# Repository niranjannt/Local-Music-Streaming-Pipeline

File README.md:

# Local Music Streaming Pipeline (ECE 445L Final Project)

This repository contains the final project for **Embedded Design Laboratory (ECE 445L)** at **UT Austin**, developed by Niranjan Telkikar, Ashton Knecht, Thompson Truong, and Nathan DeLaRosa. The project implements a music-streaming pipeline using local WAV files, combining frontend/backend software with embedded hardware.

## Project Overview

Our system streams music from a web interface to an **ESP32-Devkit-V1** and outputs audio through a **12-bit SPI DAC** connected to a headphone jack. The pipeline includes both **analog and digital filters** controlled in real-time by circular potentiometers, allowing adjustment of treble, mid, bass, and digital effects such as flanger, distortion, and reverb.

### Pipeline Flow

1. **Web Interface**: Streams WAV files via Java Serial library to the ESP32 through a USB-UART converter.  
2. **ESP32**: Receives serial data and sends it to the SPI DAC (mono channel). It also handles digital filter adjustments.  
3. **DAC**: Outputs analog audio to headphones.  
4. **TM4C123GH6PM**: Reads potentiometer inputs for analog filters and adjusts MOSFET gain circuits for treble, mid, and bass channels in real-time.  
5. **Visualizer**: Displays right-bass changes in real-time using ADC input from the TM4C.

---

## Team Contributions

- **Ashton Knecht**:  
  - Designed and soldered the PCB with ESP32-Devkit-V1.  
  - Implemented MOSFET gain circuits for analog filters.  
  - Carefully routed PCB to minimize trace length.

- **Thompson Truong**:  
  - Designed the enclosure and circular potentiometers for analog and digital filter control.  
  - Developed ESP-IDF code for digital filters on the ESP32 and analog filters on the TM4C.

- **Nathan DeLaRosa**:  
  - Implemented audio playback and backend/frontend for the web interface.  
  - Wrote ESP-IDF code for streaming audio.

- **Niranjan Telkikar**:  
  - Wrote and tested the **mono DAC_Out function** for the ESP32 (Arduino IDE/ESP-IDF).  
  - Developed a basic visualizer for real-time bass monitoring.  
  - Assisted with hardware debugging and ESP-IDF integration.

---

## Hardware Components

- ESP32-Devkit-V1  
- TM4C123GH6PM microcontroller  
- 12-bit SPI DAC (mono)  
- MOSFET-based analog gain circuits  
- Circular potentiometers for analog and digital filters  
- Headphone jack for output audio

---

## Software Components

- Arduino IDE / ESP-IDF framework for microcontroller programming  
- Java Serial library for web-to-ESP32 streaming  
- Frontend/backend web interface for music streaming  
- Real-time visualizer reading ADC inputs from TM4C

---

## Usage

1. Connect the ESP32 and TM4C to your computer via USB.  
2. Launch the web interface to stream WAV files.  
3. Adjust analog and digital filters using the circular potentiometers.  
4. Observe audio output through headphones and visualizer display.

---

## [Download a demo video of the project here!](Embedded-Lab-Final-Project-Demo.mp4)

## Acknowledgements

This project was completed as part of **ECE 445L: Embedded Design Laboratory** at **UT Austin**.

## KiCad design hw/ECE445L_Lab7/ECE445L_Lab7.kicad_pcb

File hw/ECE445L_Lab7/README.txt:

Hello, this is our rough draft of our pcb schematic and layout.
After finishing this, I believe that having the TM4C chip on the board was a mistake due to the number of analog components and pins used.

The spice model of the analog components is included in filters.asc

Thanks

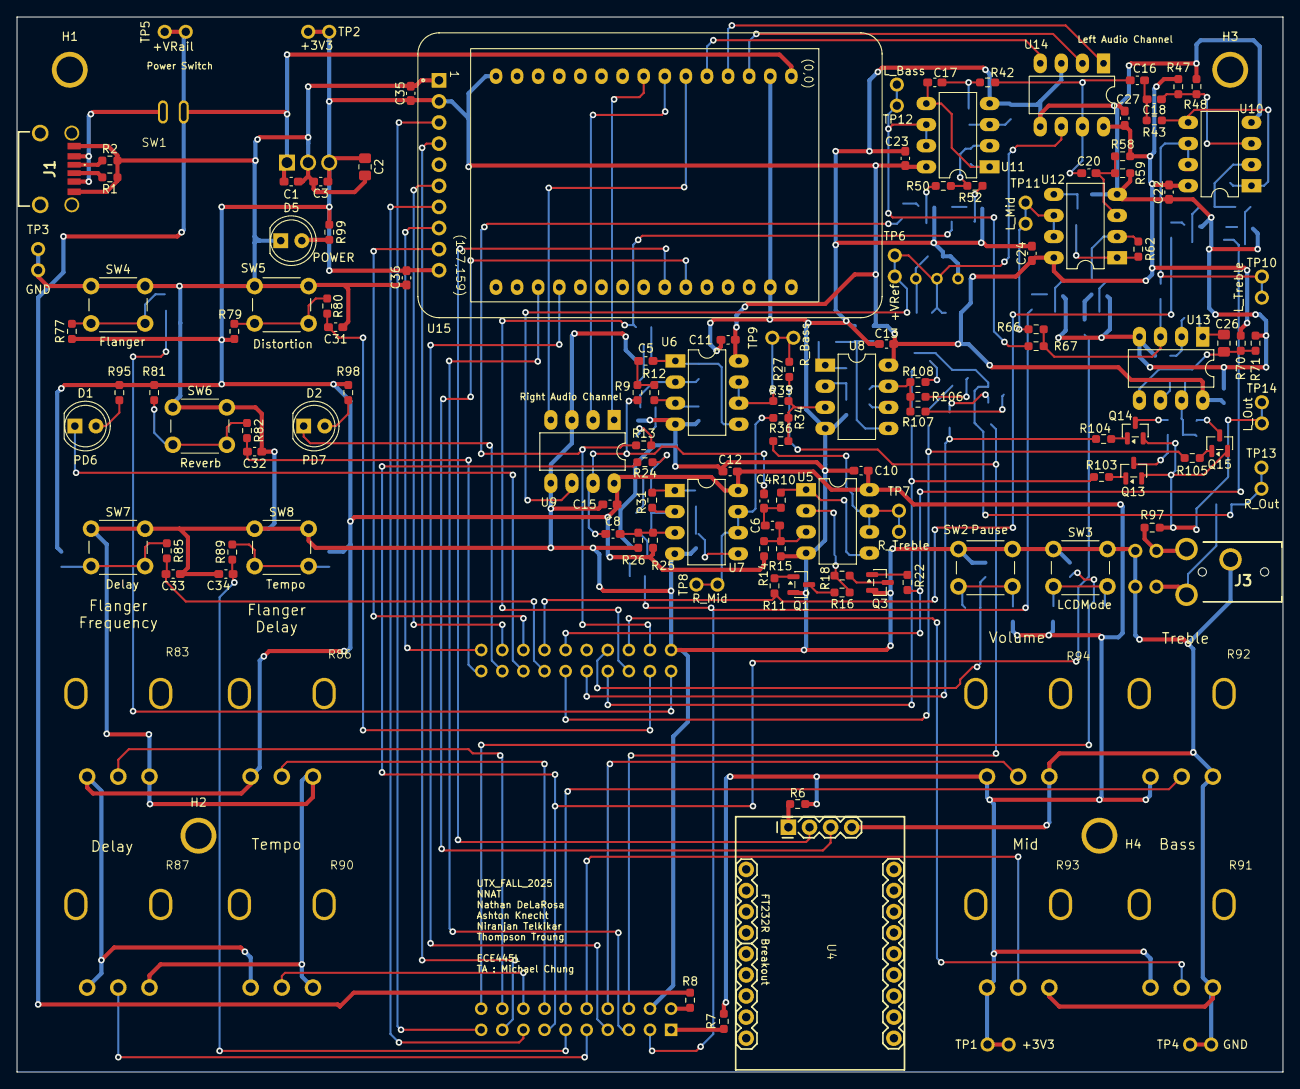
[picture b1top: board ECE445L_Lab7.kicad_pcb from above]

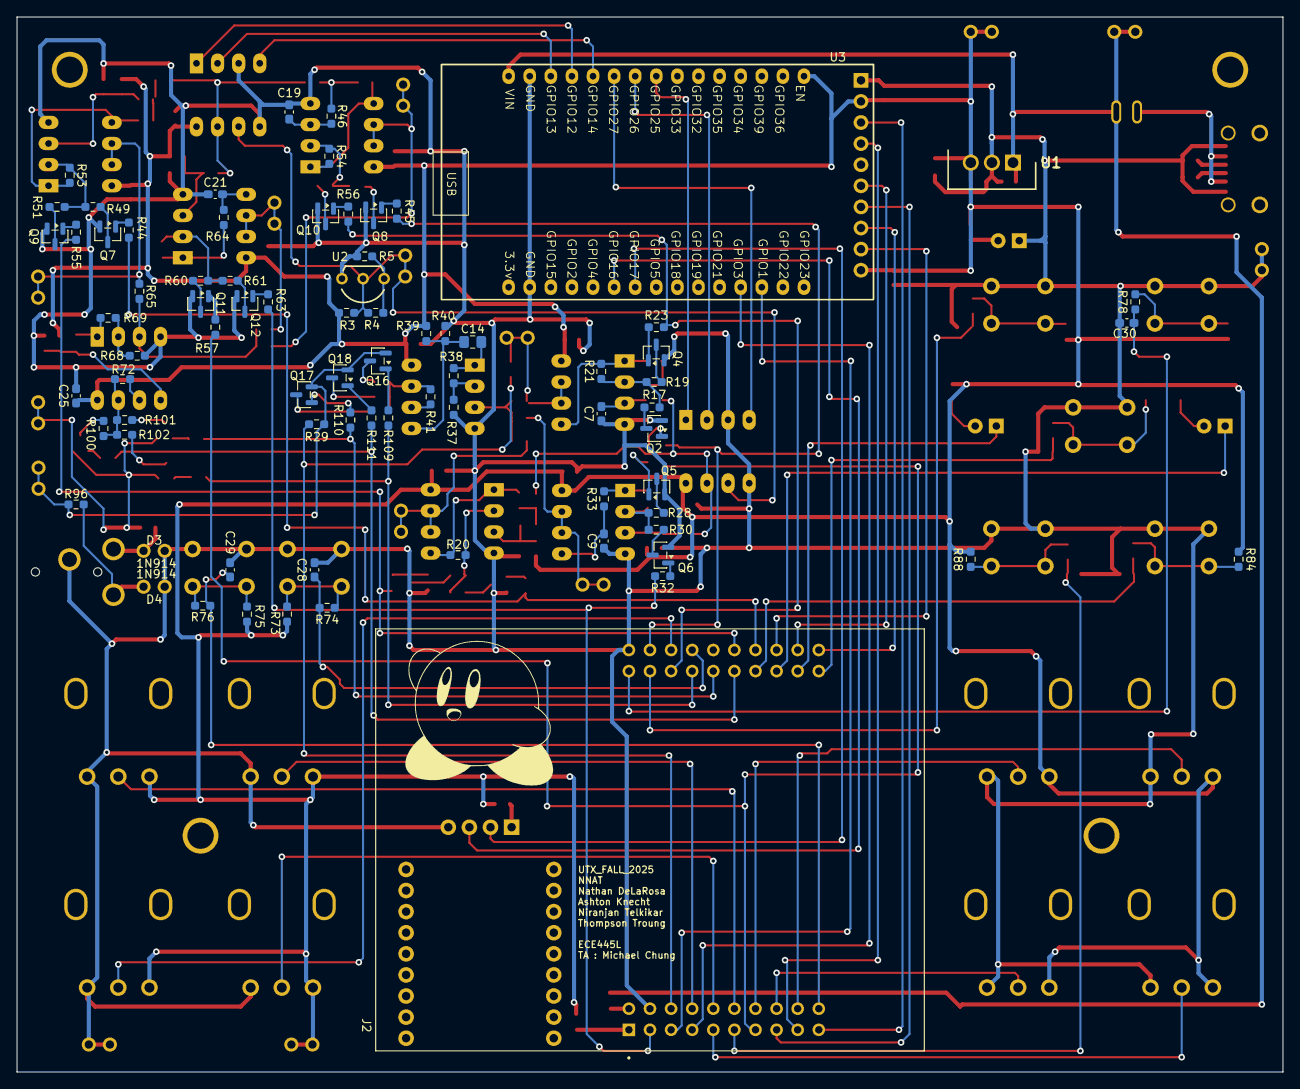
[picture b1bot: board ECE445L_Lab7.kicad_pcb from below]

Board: 2 copper layers, 152.4 x 127.0 mm, 215 parts (79 on the bottom side), 148 nets.

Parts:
C1, C3, C10, C11, C12, C13, C15, C22, C23, C24, C25, C27, C28, C29, C30, C31, C32, C33, C34: 0.1u; C_0603_1608Metric_Pad1.08x0.95mm_HandSolder
C2, C14, C26: 10u; C_0805_2012Metric_Pad1.18x1.45mm_HandSolder
C4, C6, C16, C18: 1.2n; C_0603_1608Metric_Pad1.08x0.95mm_HandSolder
C5, C7, C17, C19: 30n; C_0603_1608Metric_Pad1.08x0.95mm_HandSolder
C8, C20: 9.5n; C_0603_1608Metric_Pad1.08x0.95mm_HandSolder
C9, C21: 3.7n; C_0603_1608Metric_Pad1.08x0.95mm_HandSolder
C35, C36: 0.1uF; C_0603_1608Metric_Pad1.08x0.95mm_HandSolder
D1: PD6; LED_D5.0mm
D2: PD7; LED_D5.0mm
D3, D4: 1N914; Testpoint_1x02_P2.54mm
D5: POWER; LED_D5.0mm
G1: LOGO
H1, H2, H3, H4: MountingHole_4_40
J1: 2479774-1; 24797741
J2: EK-TM4C123GXL; ti_EKTM4C123GXL
J3: AudioJack; STX3000
Q1, Q2, Q3, Q4, Q5, Q6, Q7, Q8, Q9, Q10, Q11, Q12, Q13, Q14, Q15, Q16, Q17, Q18: MMBF170; SOT-23
R1, R2: 5K1; R_0603_1608Metric_Pad0.98x0.95mm_HandSolder
R3: 1k; R_0603_1608Metric_Pad0.98x0.95mm_HandSolder
R4: 47k; R_0603_1608Metric_Pad0.98x0.95mm_HandSolder
R5, R9, R10, R12, R20, R21, R31, R33, R35, R36, R42, R43, R46, R53, R54, R62, R64, R65, R67: 10k; R_0603_1608Metric_Pad0.98x0.95mm_HandSolder
R6, R7, R8, R27, R29: 0; R_0603_1608Metric_Pad0.98x0.95mm_HandSolder
R11, R13, R22, R23, R24, R32, R44, R45, R55, R56, R57, R63, R103, R104, R105, R109, R110, R111: 2k; R_0603_1608Metric_Pad0.98x0.95mm_HandSolder
R14, R25, R47, R58: 184k; R_0603_1608Metric_Pad0.98x0.95mm_HandSolder
R15, R26, R48, R59: 68.8k; R_0603_1608Metric_Pad0.98x0.95mm_HandSolder
R16, R17, R28, R37, R49, R50, R60, R68: 40k; R_0603_1608Metric_Pad0.98x0.95mm_HandSolder
R18, R19, R30, R51, R52, R61: 30k; R_0603_1608Metric_Pad0.98x0.95mm_HandSolder
R34, R66: 7.5k; R_0603_1608Metric_Pad0.98x0.95mm_HandSolder
R38, R69: 3.3k; R_0603_1608Metric_Pad0.98x0.95mm_HandSolder
R39, R40, R70, R71: 200k; R_0603_1608Metric_Pad0.98x0.95mm_HandSolder
R41, R72: 50k; R_0603_1608Metric_Pad0.98x0.95mm_HandSolder
R73, R75, R77, R79, R81, R84, R88: 100k; R_0603_1608Metric_Pad0.98x0.95mm_HandSolder
R74, R76, R78, R80, R82, R85, R89, R101, R107: 100; R_0603_1608Metric_Pad0.98x0.95mm_HandSolder
R83, R86, R87, R90, R91, R92, R93, R94: 10k; P120PK-Y25BR10K
R95: 1.5k; R_0603_1608Metric_Pad0.98x0.95mm_HandSolder
R96, R97: 50; R_0603_1608Metric_Pad0.98x0.95mm_HandSolder
R98, R99: 1.5V; R_0603_1608Metric_Pad0.98x0.95mm_HandSolder
R100, R106: 125; R_0603_1608Metric_Pad0.98x0.95mm_HandSolder
R102, R108: 75; R_0603_1608Metric_Pad0.98x0.95mm_HandSolder
SW1: SW_SPST; SW-T3-1A-A-A3-S1
SW2: Pause; SW_PUSH_6mm
SW3: LCDMode; SW_PUSH_6mm
SW4: Flanger; SW_PUSH_6mm
SW5: Distortion; SW_PUSH_6mm
SW6: Reverb; SW_PUSH_6mm
SW7: Delay; SW_PUSH_6mm
SW8: Tempo; SW_PUSH_6mm
TP1, TP2: +3V3; Testpoint_1x02_P2.54mm
TP3, TP4: GND; Testpoint_1x02_P2.54mm
TP5: +VRail; Testpoint_1x02_P2.54mm
TP6: +VRef; Testpoint_1x02_P2.54mm
TP7: R_Treble; Testpoint_1x02_P2.54mm
TP8: R_Mid; Testpoint_1x02_P2.54mm
TP9: R_Bass; Testpoint_1x02_P2.54mm
TP10: L_Treble; Testpoint_1x02_P2.54mm
TP11: L_Mid; Testpoint_1x02_P2.54mm
TP12: L_Bass; Testpoint_1x02_P2.54mm
TP13: R_Out; Testpoint_1x02_P2.54mm
TP14: L_Out; Testpoint_1x02_P2.54mm
U1: LM2937ET-3.3_NOPB; TO254P470X1028X1955-3P
U2: LM4041CILPR; ti_LM4041CILPR
U3: ESP32-D0WD-V3; ESP32_30pin
U4: FT232R; FT232R-Breakout
U5, U6, U7, U8, U10, U11, U12, U13: OPA2350; DIP-8_W7.62mm_LongPads
U9, U14: TLV5616; DIP-8_W7.62mm_LongPads
U15: Adafruit ST7735R; adafruit_st7735r2

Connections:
+3V3: C2.1, C3.1, C10.2, C11.2, C12.2, C13.2, C15.1, C22.2, C23.2, C24.2, C25.2, C27.1, C35.1, C36.1, R3.1, R6.1, R7.1, R14.2, R25.2, R39.2, R47.2, R58.2, R70.2, R73.1, R75.1, R77.1, R79.1, R81.1, R83.1, R84.1, R86.1, R87.1, R88.1, R90.1, R91.1, R92.1, R93.1, R94.1, R95.1, R98.1, R99.1, TP1.1 (A), TP1.2 (B), TP2.1 (A), TP2.2 (B), U1.3 (OUTPUT), U3.15 (1EN), U5.8 (V+), U6.8 (V+), U7.8 (V+), U8.8 (V+), U9.8 (VDD), U10.8 (V+), U11.8 (V+), U12.8 (V+), U13.8 (V+), U14.8 (VDD), U15.2 (VCC), U15.10 (LITE)
+VRail: C1.1, R8.1, SW1.2 (B), TP5.1 (A), TP5.2 (B), U1.1 (INPUT), U3.1 (VIN)
/Lab7_Input/Delay: R84.2, R85.1, SW7.2
/Lab7_Input/Distortion: R79.2, R80.1, SW5.2
/Lab7_Input/Flanger: R77.2, R78.1, SW4.2
/Lab7_Input/LCDMode: R75.2, R76.1, SW3.2
/Lab7_Input/Pause: R73.2, R74.1, SW2.2
/Lab7_Input/Reverb: R81.2, R82.1, SW6.2
/Lab7_Input/Tempo: R88.2, R89.1, SW8.2
ESP_IN_USB_OUT: U3.22 (GPIO17), U4.2 (TXD)
ESP_OUT_USB_IN: U3.21 (GPIO16), U4.3 (RXD)
GND: C1.2, C2.2, C3.2, C7.2, C9.1, C10.1, C11.1, C12.1, C13.1, C15.2, C19.2, C21.1, C22.1, C23.1, C24.1, C25.1, C27.2, C28.1, C29.1, C30.1, C31.1, C32.1, C33.1, C34.1, C35.2, C36.2, D3.2 (A), D4.2 (A), D5.1 (K), J1.A12 (GND_1), J1.B12 (GND_2), J2.J2_1 (GND), J2.J3_2 (GND), J3.S (sleeve), Q1.2 (S), Q2.2 (S), Q3.2 (S), Q4.2 (S), Q5.2 (S), Q6.2 (S), Q7.2 (S), Q8.2 (S), Q9.2 (S), Q10.2 (S), Q11.2 (S), Q12.2 (S), R1.1, R2.2, R5.2, R15.1, R26.1, R37.1, R40.1, R48.1, R59.1, R68.1, R71.1, R83.3, R86.3, R87.3, R90.3, R91.3, R92.3, R93.3, R94.3, SW2.1, SW3.1, SW4.1, SW5.1, SW6.1, SW7.1, SW8.1, TP3.1 (A), TP3.2 (B), TP4.1 (A), TP4.2 (B), U1.2 (GND), U2.3, U3.2 (GND), U3.17 (GND), U4.4 (GND), U5.4 (V-), U6.4 (V-), U7.4 (V-), U8.4 (V-), U9.3 (~CS), U9.5 (AGND), U10.4 (V-), U11.4 (V-), U12.4 (V-), U13.4 (V-), U14.3 (~CS), U14.5 (AGND), U15.1 (GND)
LAUDIO_CLK: U3.3 (GPIO13), U14.2 (SCLK)
LAUDIO_FS: U3.5 (GPIO14), U14.4 (FS)
LAUDIO_OUT: U3.4 (GPIO12), U14.1 (DIN)
L_AudioBuf: R72.1, R100.1, R101.2, R102.2, U13.7
L_AudioOut: Q13.2 (S), Q14.2 (S), Q15.2 (S), R97.2, TP14.1 (A), TP14.2 (B)
L_Bass: R67.1, TP12.1 (A), TP12.2 (B), U11.6 (-), U11.7
L_Buff: C26.1, R69.2, U13.1
L_Mid: R66.1, TP11.1 (A), TP11.2 (B), U12.6 (-), U12.7
L_Treble: R65.1, TP10.1 (A), TP10.2 (B), U10.6 (-), U10.7
unnamed: C4.2, C6.1, R10.2
unnamed: C5.2, R9.1, R12.1
unnamed: C16.2, C18.1, R43.2
unnamed: C17.2, R42.2, R46.1
unnamed: D1.2 (A), R95.2
unnamed: D2.2 (A), R98.2
unnamed: D3.1 (K), J3.T (tip), R97.1
unnamed: D4.1 (K), J3.R (ring), R96.1
unnamed: D5.2 (A), R99.2
unnamed: J1.A5 (CC1), R1.2
unnamed: J1.B5 (CC2), R2.1
unnamed: J1.A9 (VBUS_1), J1.B9 (VBUS_2), SW1.1 (A)
unnamed: J2.J1_1 (+3.3V), R7.2
unnamed: J2.J3_1 (+VBUS), R8.2
unnamed: Q1.3 (D), R16.2
unnamed: Q1.1 (G), R11.2
unnamed: Q2.3 (D), R17.2
unnamed: Q2.1 (G), R13.2
unnamed: Q3.3 (D), R18.1
unnamed: Q3.1 (G), R22.1
unnamed: Q4.3 (D), R19.1
unnamed: Q4.1 (G), R23.1
unnamed: Q5.3 (D), R28.2
unnamed: Q5.1 (G), R24.2
unnamed: Q6.3 (D), R30.1
unnamed: Q6.1 (G), R32.1
unnamed: Q7.3 (D), R49.2
unnamed: Q7.1 (G), R44.2
unnamed: Q8.3 (D), R50.2
unnamed: Q8.1 (G), R45.2
unnamed: Q9.3 (D), R51.2
unnamed: Q9.1 (G), R55.1
unnamed: Q10.3 (D), R52.2
unnamed: Q10.1 (G), R56.1
unnamed: Q11.3 (D), R60.2
unnamed: Q11.1 (G), R57.2
unnamed: Q12.3 (D), R61.2
unnamed: Q12.1 (G), R63.1
unnamed: Q13.3 (D), R102.1
unnamed: Q13.1 (G), R103.2
unnamed: Q14.3 (D), R101.1
unnamed: Q14.1 (G), R104.2
unnamed: Q15.3 (D), R100.2
unnamed: Q15.1 (G), R105.2
unnamed: Q16.3 (D), R108.1
unnamed: Q16.1 (G), R109.2
unnamed: Q17.3 (D), R107.1
unnamed: Q17.1 (G), R110.2
unnamed: Q18.3 (D), R106.1
unnamed: Q18.1 (G), R111.2
unnamed: R4.2, R5.1, U2.1
unnamed: R31.2, R33.1, U7.1
unnamed: R62.2, R64.1, U12.1
unnamed: R6.2, U4.1 (3V3)
unnamed: C6.2, R14.1, R15.2, U5.3 (+)
unnamed: R16.1, R18.2, R20.1, U5.2 (-)
unnamed: R10.1, R20.2, U5.1, U5.5 (+)
unnamed: C7.1, R12.2, U6.3 (+)
unnamed: R17.1, R19.2, R21.1, U6.2 (-)
unnamed: C5.1, R21.2, U6.1, U6.5 (+)
unnamed: C8.2, R25.1, R26.2, U7.3 (+)
unnamed: R28.1, R30.2, R31.1, U7.2 (-)
unnamed: C9.2, R33.2, U7.5 (+)
unnamed: R34.2, R35.2, R36.1, U8.3 (+)
unnamed: R37.2, R38.1, U8.2 (-)
unnamed: C14.2, R39.1, R40.2, U8.5 (+)
unnamed: R41.2, U8.6 (-)
unnamed: C18.2, R47.1, R48.2, U10.3 (+)
unnamed: R49.1, R51.1, R53.1, U10.2 (-)
unnamed: R43.1, R53.2, U10.1, U10.5 (+)
unnamed: C19.1, R46.2, U11.3 (+)
unnamed: R50.1, R52.1, R54.1, U11.2 (-)
unnamed: C17.1, R54.2, U11.1, U11.5 (+)
unnamed: C20.2, R58.1, R59.2, U12.3 (+)
unnamed: R60.1, R61.1, R62.1, U12.2 (-)
unnamed: C21.2, R64.2, U12.5 (+)
unnamed: R65.2, R66.2, R67.2, U13.3 (+)
unnamed: R68.2, R69.1, U13.2 (-)
unnamed: C26.2, R70.1, R71.2, U13.5 (+)
unnamed: R72.2, U13.6 (-)
PA2: J2.J2_10 (PA2), U15.8 (SCK)
PA3: J2.J2_9 (PA3), U15.6 (TFT_CS)
PA4: J2.J2_8 (PA4), U15.9 (MISO)
PA5: J2.J1_8 (PA5), U15.7 (MOSI)
PA6: J2.J1_9 (PA6), U15.4 (D/C)
PA7: J2.J1_10 (PA7), U15.3 (RESET)
PB0: J2.J1_3 (PB0), U3.28 (GPIO1)
PB1: J2.J1_4 (PB1), U3.27 (GPIO3)
PB2: J2.J2_2 (PB2), R13.1, R45.1
PB3: J2.J4_3 (PB3), R23.2, R56.2
PB4: J2.J1_7 (PB4), R24.1, R57.1
PB5: J2.J1_2 (PB5), R32.2, R63.2
PB6: J2.J2_7 (PB6), R11.1, R44.1
PB7: J2.J2_6 (PB7), R22.2, R55.2
PC4: J2.J4_4 (PC4), R103.1, R109.1
PC5: J2.J4_5 (PC5), R104.1, R110.1
PC6: J2.J4_6 (PC6), R105.1, R111.1
PC7: C33.2, J2.J4_7 (PC7), R85.2
PD0: J2.J3_3 (PD0), R27.1, R29.1
PD1: J2.J3_4 (PD1), R94.2
PD2: J2.J3_5 (PD2), R93.2
PD3: J2.J3_6 (PD3), R92.2
PD6: D1.1 (K), J2.J4_8 (PD6)
PD7: D2.1 (K), J2.J4_9 (PD7)
PE0: J2.J2_3 (PE0), R91.2
PE1: J2.J3_7 (PE1), R86.2
PE2: J2.J3_8 (PE2), R90.2
PE3: J2.J3_9 (PE3), R83.2
PE4: J2.J1_5 (PE4), R87.2
PE5: C34.2, J2.J1_6 (PE5), R89.2
PF0: C28.2, J2.J2_4 (PF0), R74.2
PF1: C29.2, J2.J3_10 (PF1), R76.2
PF2: C30.2, J2.J4_1 (PF2), R78.2
PF3: C31.2, J2.J4_2 (PF3), R80.2
PF4: C32.2, J2.J4_10 (PF4), R82.2
RAUDIO_CLK: U3.7 (GPIO26), U9.2 (SCLK)
RAUDIO_FS: U3.6 (GPIO27), U9.4 (FS)
RAUDIO_OUT: U3.8 (GPIO25), U9.1 (DIN)
R_AudioBuf: R41.1, R106.2, R107.2, R108.2, U8.7
R_AudioOut: Q16.2 (S), Q17.2 (S), Q18.2 (S), R29.2, R96.2, TP13.1 (A), TP13.2 (B)
R_Bass: R27.2, R35.1, TP9.1 (A), TP9.2 (B), U6.6 (-), U6.7
R_Buff: C14.1, R38.2, U8.1
R_Mid: R34.1, TP8.1 (A), TP8.2 (B), U7.6 (-), U7.7
R_Treble: R36.2, TP7.1 (A), TP7.2 (B), U5.6 (-), U5.7
VRef: R3.2, R4.1, TP6.1 (A), TP6.2 (B), U2.2, U9.6 (REF), U14.6 (REF)
Vin_L: C16.1, C20.1, R42.1, U14.7 (OUT)
Vin_R: C4.1, C8.1, R9.2, U9.7 (OUT)

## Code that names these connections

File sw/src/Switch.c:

// File **********Switch.c***********
// Spring 2025
// define your hardware interface
#include <stdint.h>
#include "../inc/tm4c123gh6pm.h"
#include "Timers.h"
#include "Switch.h"
#include "../inc/SysTickInts.h"
#include "../inc/TLV5616.h"
/*
 * PF0 - Pause
 * PF1 - LCDMode
 * PF2 - Flanger
 * PF3 - Distortion
 * PF4 - Reverb
 * PC7 - Delay
 * PE5 - Tempo
 */

void SwitchInit() {
    SYSCTL_RCGCGPIO_R |= 0x34;       //activate clock for port F, C, and E
    while((SYSCTL_PRGPIO_R&0x34) == 0){}; // wait
    GPIO_PORTF_DIR_R &= ~0x1F;      //set input for PF0-4
    GPIO_PORTF_DEN_R |= 0x1F;       //set digital enable for PF0-4

    GPIO_PORTC_DIR_R &= ~0x80; // set input for PC7
    GPIO_PORTC_DEN_R |= 0x80; // digital enable PC7

    GPIO_PORTE_DIR_R &= ~0x20; // input PE5
    GPIO_PORTE_DEN_R |= 0x20; // digital enable PE5
}
/*
 * Read switch inputs as a bit vector
 */
uint16_t SwitchIn() {
    return (GPIO_PORTF_DATA_R & 0x1F) & (GPIO_PORTC_DATA_R & 0x80) & (GPIO_PORTE_DATA_R & 0x20);
    // F - 1, 2, 4, 8, 16 C - 128 E - 32
}

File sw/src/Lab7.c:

// Lab5.c
// Runs on TM4C123
// Spring 2025

/*
// *******Inputs from switches**************************
// bit1 PE1 Voice switch, positive logic switch, external pull down
// bit0 PE0 Play switch, positive logic switch, external pull down

// ********Outputs to DAC****************************
// TLV5616 SSIClk (SCLK) connected to PD0
// TLV5616 SSIFss (FS)   connected to PD1
// TLV5616 SSITx (DIN)   connected to PD3

// *****LCD graphics, and I/O with SDC***************
// Backlight (pin 10) connected to +3.3 V
// MISO (pin 9) connected to PA4 (SSIRx for SDC)
/+/ SCK (pin 8) connected to PA2 (SSI0Clk)
// MOSI (pin 7) connected to PA5 (SSI0Tx)
// TFT_CS (pin 6) connected to PA3 (SSI0Fss)
// CARD_CS (pin 5) connected to PD7 (CS for SDC)
// Data/Command (pin 4) connected to PA6 (GPIO)
// RESET (pin 3) connected to PA7 (GPIO)
// VCC (pin 2) connected to +3.3 V
// Gnd (pin 1) connected to ground

// Debugging, oscilloscope connected to 
// PF1 toggles in background
// PF3 toggles in foreground
*/

#include <stdint.h>
#include "../inc/tm4c123gh6pm.h"
#include "../inc/PLL.h"
#include "Switch.h"
#include "../inc/SysTickInts.h"
#include "../inc/TLV5616.h"
#include "../inc/ST7735.h"
#include "../inc/Timer0A.h"
#include "../inc/Timer1A.h"
#include "../inc/Timer2A.h"
#include "../inc/TLV5616.h"
#include "AudioCommands.h"
void DisableInterrupts(void); // Disable interrupts
void EnableInterrupts(void);  // Enable interrupts
void WaitForInterrupt(void);  // low power mode

_Bool changeVolumes = 1;
unsigned bassVol = 0;
unsigned midVol = 0;
unsigned trebVol = 0;
unsigned mainVol = 0;
void Visualize(void);
void ADC_Init(void);

int main(void){
  DisableInterrupts();
  PLL_Init(Bus80MHz);    // bus clock at 80 MHz
  AudioCommandInit(); // initializes UART, Switches and Potentiometer
  ADC_Init();
  EnableInterrupts();
  ST7735_InitR(INITR_REDTAB);     // Start up display.


  while(1){
    //UpdateLCD();
      Visualize();
      //UpdateLCD();

   }
}
   

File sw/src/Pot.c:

#include <stdint.h>
#include "../inc/tm4c123gh6pm.h"
#include "Timers.h"
#include "Pot.h"
#include "../inc/SysTickInts.h"
#include "../inc/TLV5616.h"
#include "AudioCommands.h"

/*
 * PE0 - Bass           -   AIN3
 * PD2 - Mid            -   AIN5
 * PD3 - Treble         -   AIN4
 * PD1 - Volume         -   AIN6
 * PE3 - Flanger Freq   -   AIN0
 * PE1 - Flanger Delay  -   AIN2
 * PE4 - Delay          -   AIN9
 * PE2 - Tempo          -   AIN1
 */


void PotInit() {
    //ADC and Clock initializations
    SYSCTL_RCGCADC_R |= 0x0002;               // 1) activate ADC1
    SYSCTL_RCGCGPIO_R |= 0x18;                // 2) activate clock for Port E and Port D
    while((SYSCTL_PRGPIO_R&0x18) != 0x18){};  // 3) for stabilization

    //Port E initializations
    GPIO_PORTE_DIR_R &= ~0x1F;    // 4) make PE0-4 input
    GPIO_PORTE_AFSEL_R |= 0x1F;   // 5) Set the direction of PE0-4 as input
    GPIO_PORTE_DEN_R &= ~0x1F;    // 6) Enable alternative function for PE0-4 (Alternative signal rather than GPIO)
    GPIO_PORTE_AMSEL_R |= 0x1F;   // 7) enable analog functionality on PE0-4

    //Port D initializations
    GPIO_PORTD_DIR_R &= ~0x0F;    // 4) make PD0-3 input
    GPIO_PORTD_AFSEL_R |= 0x0F;   // 5) Set the direction of PD0-3 as input
    GPIO_PORTD_DEN_R &= ~0x0F;    // 6) Enable alternative function for PD0-3 (Alternative signal rather than GPIO)
    GPIO_PORTD_AMSEL_R |= 0x0F;   // 7) enable analog functionality on PD0-3


    ADC1_PC_R &= ~0xF;
    ADC1_PC_R |= 0x1;             // 8) configure for 125K samples/sec
    ADC1_SSPRI_R = 0x0330;        // 9) Sequencer 3 and 0 are highest priority
    ADC1_ACTSS_R &= ~0x9;      // 10) disable sample sequencer 3 and 0
    ADC1_EMUX_R &= ~0xF00F;       // 11) seq3 and 0 are software triggered

    ADC1_SSMUX3_R &= ~0xF;
    ADC1_SSMUX3_R |= 0x7;   // 12) Sample 1 correlates to Analog input 7 respectively

    ADC1_SSMUX0_R &= ~0xFFFFFFFF;
    ADC1_SSMUX0_R |= 0x09206453; // Samples

    ADC1_SSCTL3_R = 0x0006;       // 13) no TS0 D0, yes IE0 END0
    ADC1_SSCTL0_R &= 0x00;
    ADC1_SSCTL0_R |= 0xC0000000; // IE7 + END7
    ADC1_IM_R &= ~0x9;         // 14) disable SS3 and SS0 interrupts
    ADC1_ACTSS_R |= 0x9;       // 15) enable sample sequencer 3 and 0
}

/*
 * Read in values from potentiometers
 */
void PotIn(uint16_t* data) {
    ADC1_PSSI_R = 0x0001;            // 1) initiate SS0
    while((ADC1_RIS_R&0x01)==0){};   // 2) wait for conversion done
    data[0] = ADC1_SSFIFO0_R&0xFFF;  //
    data[1] = ADC1_SSFIFO0_R&0xFFF;  //
    data[2] = ADC1_SSFIFO0_R&0xFFF;  //
    data[3] = ADC1_SSFIFO0_R&0xFFF;  //
    data[4] = ADC1_SSFIFO0_R&0xFFF;  //
    data[5] = ADC1_SSFIFO0_R&0xFFF;  //
    data[6] = ADC1_SSFIFO0_R&0xFFF;  //
    data[7] = ADC1_SSFIFO0_R&0xFFF;  //
    ADC1_ISC_R = 0x0001;
}

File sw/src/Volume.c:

/*
 * Volume.c
 *
 *  Created on: Dec 2, 2025
 *      Author: Ashton
 */
#include <stdint.h>
#include "../inc/tm4c123gh6pm.h"
#include "Volume.h"

//const uint32_t bassSettings = {0x00, 0x08, 0x04, 0x0C};
//const uint32_t middSettings = {0x00, 0x20, 0x10, 0x30};
//const uint32_t trebSettings = {0x00, 0x80, 0x40, 0xC0};
//
//#define PB0   (*((volatile uint32_t *)0x40005004))
//#define PB1   (*((volatile uint32_t *)0x40005008))
//#define PB2   (*((volatile uint32_t *)0x4000500C))
//#define PB3   (*((volatile uint32_t *)0x40005010))
//#define PB4   (*((volatile uint32_t *)0x40005014))
//#define PB5   (*((volatile uint32_t *)0x40005018))
//#define PB6   (*((volatile uint32_t *)0x4000501C))
//#define PB7   (*((volatile uint32_t *)0x40005020))

void Clock_Delay1ms(uint32_t n);
void Clock_Delay(uint32_t ulCount);

void initVolume() {
    SYSCTL_RCGCGPIO_R |= 0x06;  // activate clock for Port B and C
    Clock_Delay1ms(1);

    GPIO_PORTB_DIR_R |= 0x00FC;         // PB2, PB3, PB4, PB5, PB6, PB7 out
    GPIO_PORTB_DEN_R |= 0x00FC;         // enable digital I/O on PB2, PB3, PB4, PB5, PB6, PB7
    GPIO_PORTB_DATA_R &= ~(0x00FC);          // Initialize the Pins to Off


    GPIO_PORTC_DIR_R |= 0x70;         // PC4, PC5, PC6
    GPIO_PORTC_DEN_R |= 0x70;
    GPIO_PORTC_DATA_R &= ~(0x30);
    GPIO_PORTC_DATA_R |= (0x40);
}




void setBass(unsigned input){
    switch (input) {
    case 0 :
        GPIO_PORTB_DATA_R &= ~(0x0C);
        break;
    case 1 :
        GPIO_PORTB_DATA_R &= ~(0x08);
        GPIO_PORTB_DATA_R |= (0x04);
        break;
    case 2 :
        GPIO_PORTB_DATA_R &= ~(0x04);
        GPIO_PORTB_DATA_R |= (0x08);
        break;
    case 3 :
        GPIO_PORTB_DATA_R |= (0x0C);
        break;
    default :
        GPIO_PORTB_DATA_R &= ~(0x0C);
    }

}

void setMid(unsigned input){
    switch (input) {
    case 0 : // 0 - 1023
        GPIO_PORTB_DATA_R &= ~(0x30);
        break;
    case 1 : // 1024 - 2046
        GPIO_PORTB_DATA_R &= ~(0x20);
        GPIO_PORTB_DATA_R |= (0x10);
        break;
    case 2 : // 2047 - 3069
        GPIO_PORTB_DATA_R &= ~(0x10);
        GPIO_PORTB_DATA_R |= (0x20);
        break;
    case 3 : // 3070 - 4095
        GPIO_PORTB_DATA_R |= (0x30);
        break;
    default :
        GPIO_PORTB_DATA_R &= ~(0x30);
    }

}

void setTreb(unsigned input){
    switch (input) {
    case 0 :
        GPIO_PORTB_DATA_R &= ~(0xC0);
        break;
    case 1 :
        GPIO_PORTB_DATA_R &= ~(0x80);
        GPIO_PORTB_DATA_R |= (0x40);
        break;
    case 2 :
        GPIO_PORTB_DATA_R &= ~(0x40);
        GPIO_PORTB_DATA_R |= (0x80);
        break;
    case 3 :
        GPIO_PORTB_DATA_R &= ~(0x40);
        GPIO_PORTB_DATA_R |= (0x80);
        break;
    default :
        GPIO_PORTB_DATA_R &= ~(0xC0);
    }

}

void setVolume(unsigned input){
    switch (input) {
    case 0 : // 0 - 585
        GPIO_PORTC_DATA_R &= ~(0x30);
        GPIO_PORTC_DATA_R |= (0x40);
        break;
    case 1 : // 586 - 1170
        GPIO_PORTC_DATA_R &= ~(0x50);
        GPIO_PORTC_DATA_R |= (0x20);
        break;
    case 2 : // 1171 - 1755
        GPIO_PORTC_DATA_R &= ~(0x60);
        GPIO_PORTC_DATA_R |= (0x10);
        break;
    case 3 : // 1756 - 2340
        GPIO_PORTC_DATA_R &= ~(0x10);
        GPIO_PORTC_DATA_R |= (0x60);
        break;
    case 4 : // 2341 - 2925
        GPIO_PORTC_DATA_R &= ~(0x20);
        GPIO_PORTC_DATA_R |= (0x50);
        break;
    case 5 : // 2926 - 3510
        GPIO_PORTC_DATA_R &= ~(0x40);
        GPIO_PORTC_DATA_R |= (0x30);
        break;
    case 6 : // 3511 - 4095
        GPIO_PORTC_DATA_R |= (0x70);
        break;
    default :
        GPIO_PORTC_DATA_R |= (0x70);
    }

}




void Clock_Delay(uint32_t ulCount){
  while(ulCount){
    ulCount--;
  }
}

// ------------Clock_Delay1ms------------
// Simple delay function which delays about n milliseconds.
// Inputs: n, number of msec to wait
// Outputs: none
void Clock_Delay1ms(uint32_t n){
  while(n){
    Clock_Delay(23746);  // 1 msec, tuned at 80 MHz, originally part of LCD module
    n--;
  }
}

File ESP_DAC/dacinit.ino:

#include <SPI.h>

#define LAUDIO_FS 14
#define RAUDIO_FS 27
#define RAUDIO_CLK 26
#define RAUDIO_OUT 25
#define LAUDIO_CLK 13
#define LAUDIO_OUT 12

SPIClass spileft(VSPI);
SPIClass spiright(HSPI);
void DAC_Init_Left(){
pinMode(LAUDIO_FS, OUTPUT);
digitalWrite(LAUDIO_FS, HIGH);
spileft.begin(LAUDIO_CLK, -1, LAUDIO_OUT, -1);



}

void DAC_Init_Right(){
pinMode(RAUDIO_FS, OUTPUT);
digitalWrite(RAUDIO_FS, HIGH);
spiright.begin(RAUDIO_CLK, -1, RAUDIO_OUT, -1);

}

void DAC_Out_Left(uint16_t left_channel_data){
spileft.beginTransaction(SPISettings(10000000, MSBFIRST, SPI_MODE2));
digitalWrite(LAUDIO_FS, LOW);
spileft.transfer16(0x4000|(left_channel_data&0x0fff));
digitalWrite(LAUDIO_FS, HIGH);
spileft.endTransaction();

}

void DAC_Out_Right(uint16_t right_channel_data){
spiright.beginTransaction(SPISettings(10000000, MSBFIRST, SPI_MODE2));
digitalWrite(RAUDIO_FS, LOW);
spiright.transfer16(0x4000|(right_channel_data&0x0fff));
digitalWrite(RAUDIO_FS, HIGH);
spiright.endTransaction();

}

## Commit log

2025-10-15 Prep Flatten
2025-10-15 Flatten
2025-10-16 Lab document update Fall 2025
2025-10-19 add deadline
2025-10-20 Created spice models for analog circuits, started kicad schematic -> right audio channel, screen, basic power
2025-10-20 Small filter changes :P
2025-10-22 Updated hardware schematic
2025-10-22 updated BOM
2025-10-22 Added System Diagram
2025-10-22 Updated Schematic
2025-10-22 More Updates to hardware
2025-10-23 added initial draft for sending sample rate through the port
2025-10-24 sending init data after sample rate
2025-10-26 Simple UART Read Test from USB-UART Adapter
2025-10-26 cleaned up audio file
2025-10-26 added event listener
2025-10-26 oops accidentally pushed an error lol
2025-10-27 tm4c starter code
2025-10-27 Lab7A Schematic and BOM - Ashton
2025-10-27 switches and pots inits
2025-10-27 jk this is the inits
2025-10-29 Made changers to the schematic, updated bom, and created priliminary layout for the PCB. Ready for 7B Prep!
2025-10-29 Pushing layout for merge
2025-10-31 Parts layout part 2
2025-10-31 Rough draft layout - need to remove tm4c chip
2025-10-31 Screen and ESP DAC code
2025-10-31 report
2025-11-01 Added current consumption to schematic
2025-11-01 Updated lab7a report
2025-11-01 cleaned up java directory
2025-11-01 Updated bom, ready for lab7a report
2025-11-03 PCB Layout
2025-11-03 Hardware layout - fixed voltage reference
2025-11-03 DACOut, Buffer, and Screen
2025-11-04 esp debug
2025-11-04 Pushing so i can work on my desktop
2025-11-04 working send and receive using small tests
2025-11-04 Final PCB commit
2025-11-05 fixed java reading wav
2025-11-08 Updated bom for lab 7B
2025-11-14 added webapp directory and put current frontend in it
2025-11-14 ugh, round 2 it is
2025-11-14 PE0-3 -> PE0-4
2025-11-18 Fixed ADC Init Error Redefined
2025-11-20 Ported over code
2025-11-20 Finished inputs and uart v1 (NOT TESTED)
2025-11-23 Polling for Receiving Data ESP
2025-11-26 esp code
2025-11-26 esp stuff
2025-11-26 sorry boys couldnt get it workin tonight
2025-11-29 a bunch of random stuff trying to get it to work
2025-11-29 test for ashton to run
2025-11-29 Pushing nathan's stuff
2025-11-29 two buffer attempt
2025-11-29 ESP double fifo work
2025-11-29 arduino ide was not saved
2025-11-29 fixed uart0 to uart1
2025-11-29 fixing ADC code
2025-11-30 added arduino code
2025-11-30 pot.c pass by reference
2025-11-30 down sampling
2025-11-30 added preliminary values for FX
2025-11-30 Changed Serial
2025-12-01 somejava changes
2025-12-02 working sound LETS GOOOOOO
2025-12-03 Removed virtural registers from virtRegOut when spilled due to tied operands
2025-12-03 Update DSPFX.ino with testing code
2025-12-03 Update TM4C2ESP.ino with test code
2025-12-03 Update AudioCommands.c test code
2025-12-03 Untested Visualizer Code + Kendrick Songs Added
2025-12-03 Fixed analog volume control - 1 and 2 are still switched
2025-12-03 Update Pot.c (Everything Seems to Work Now)
2025-12-03 Update Pot.h (Changed to uint16_t)
2025-12-03 Update AudioCommands.c (Should be working now)
2025-12-03 Update Switch.c (uint16_t)
2025-12-03 Update Switch.h (uint16_t)
2025-12-03 Update TM4C2ESP.ino (ESP Receiver works)
2025-12-03 Update DSPFX.ino preliminary
2025-12-03 Added Volume Control to AudioCommands.c
2025-12-04 Finished Visualizer
2025-12-04 Ashton stash
2025-12-04 initilized adc for testing
2025-12-04 Fixed Point FX
2025-12-04 Tested and did bug fixes to knobs, changed visualizer to use PD0 like required on the PCB - Bass, Mid, Treble and Volume/Analog Distortion all work - sound works with Need 2
2025-12-04 Mini fix for treble
2025-12-04 ESP changes for webapp
2025-12-04 completed web app
2025-12-04 pls merge
2025-12-04 upadted git ignore
2025-12-04 wat3
2025-12-04 delted ds store?
2025-12-04 Changed Bass Input from PE4 to PD0
2025-12-04 web app update:
2025-12-04 removed ds store files
2025-12-04 Remove DS_Store files from main
2025-12-04 verify fix for static java
2025-12-04 WIP before switching branches
2025-12-17 Pushing Local Music Streaming Pipeline Files
2025-12-17 Revise README with project details and usage
    Updated README to provide detailed project overview, team contributions, and usage instructions.
2025-12-17 Update README with ESP-IDF code details
2025-12-17 Adding Embedded Lab Final Project Demo Video
2025-12-17 Add demo video link to README
2025-12-17 Update demo video link in README
